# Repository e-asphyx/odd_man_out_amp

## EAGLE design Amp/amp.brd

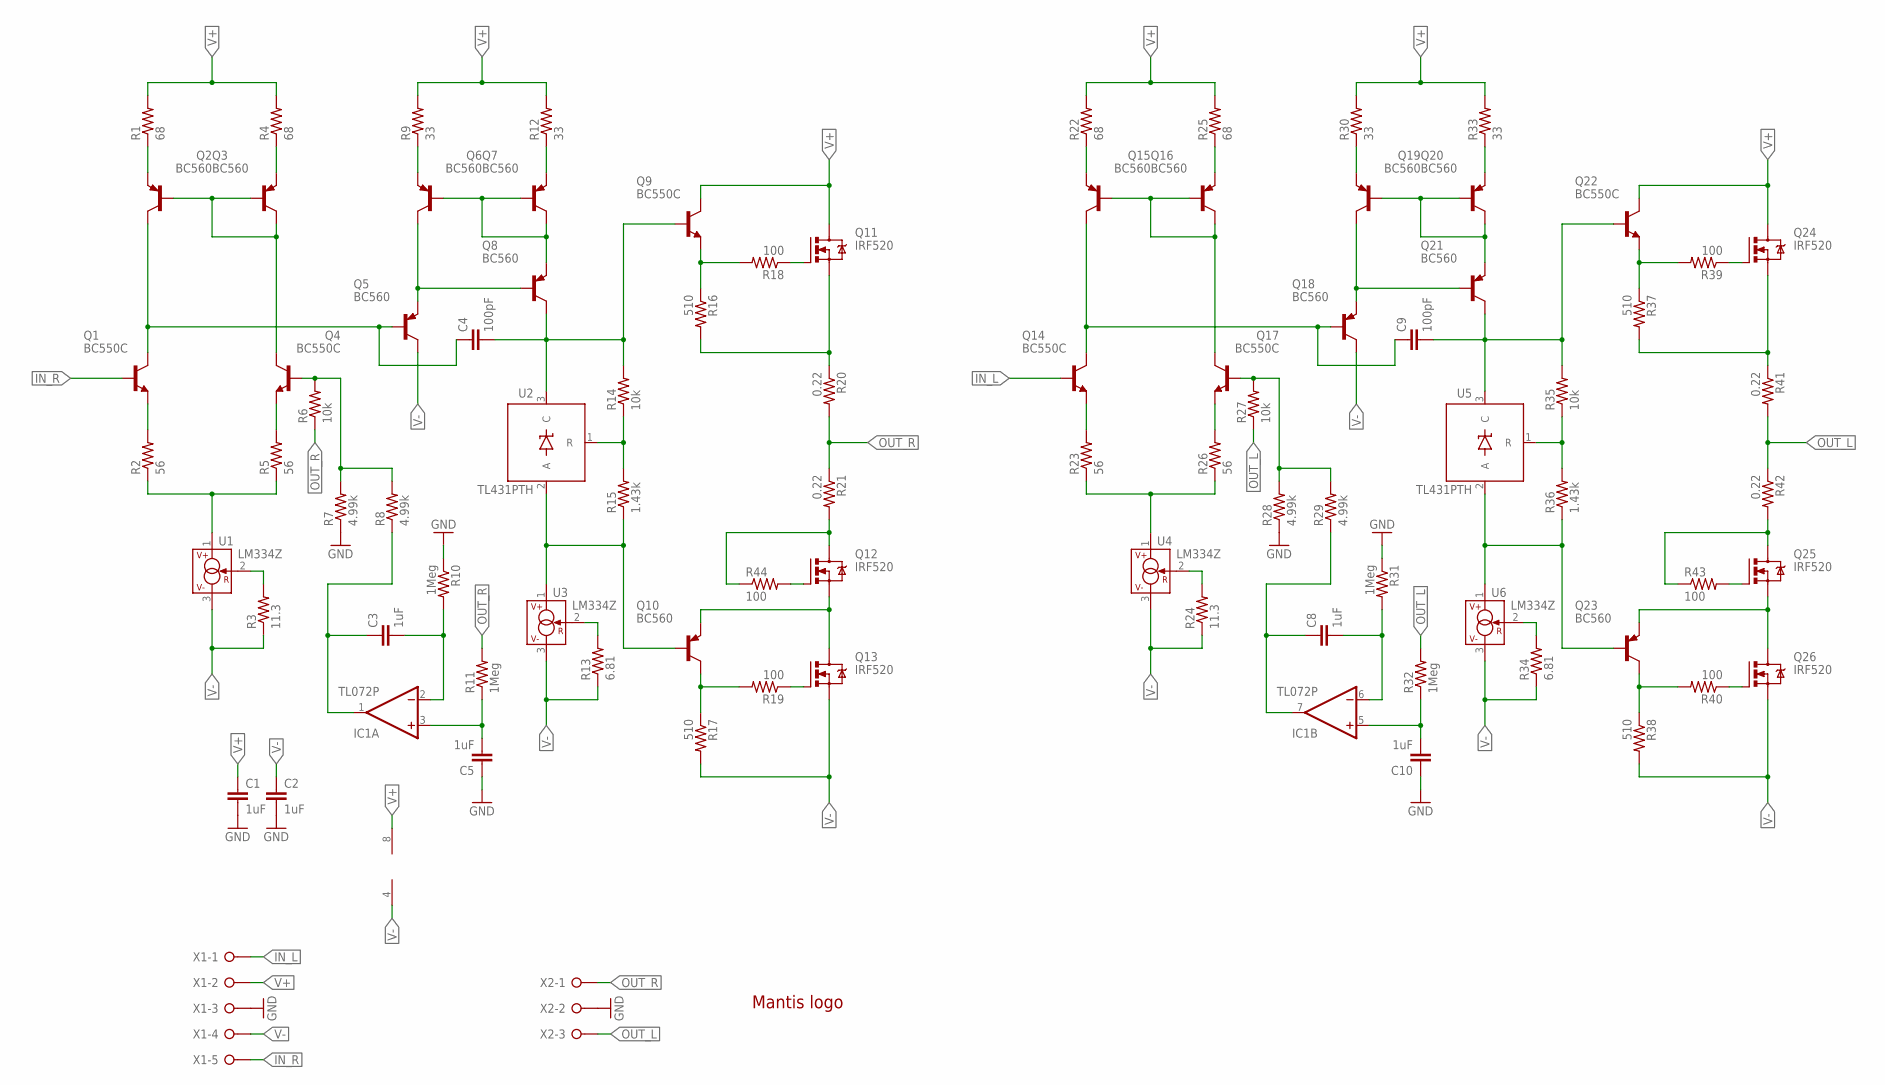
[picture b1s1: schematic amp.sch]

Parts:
C1, C2: 1uF; CAP-PTH-SMALL
C3, C5, C8, C10: 1uF; C5B5.5
C4, C9: 100pF; C5B4.5
IC1: TL072P; DIL08
LOGO1: LOGO-MANTIS
Q1, Q4, Q9, Q14, Q17, Q22: BC550C; TO92-EBC
Q2, Q3, Q5, Q6, Q7, Q8, Q10, Q15, Q16, Q18, Q19, Q20, Q21, Q23: BC560; TO92-EBC
Q11, Q12, Q13, Q24, Q25, Q26: IRF520; TO220BV
R1, R4, R22, R25: 68; AXIAL-0.4
R2, R5, R23, R26: 56; AXIAL-0.4
R3, R24: 11.3; AXIAL-0.4
R6, R14, R27, R35: 10k; AXIAL-0.4
R7, R8, R28, R29: 4.99k; AXIAL-0.4
R9, R12, R30, R33: 33; AXIAL-0.4
R10, R11, R31, R32: 1Meg; AXIAL-0.4
R13, R34: 6.81; AXIAL-0.4
R15, R36: 1.43k; AXIAL-0.4
R16, R17, R37, R38: 510; AXIAL-0.4
R18, R19, R39, R40, R43, R44: 100; AXIAL-0.4
R20, R21, R41, R42: 0.22; AXIAL-0.4
U1, U3, U4, U6: LM334Z; TO-92
U2, U5: TL431PTH; TO-92
X1: W237-05P; W237-5P
X2: W237-3E

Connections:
GND: C1.2, C2.2, C5.1, C10.1, R7.P$1 (1), R10.P$1 (1), R28.P$1 (1), R31.P$1 (1), X1.3, X2.2
IN_L: Q14.B, X1.1
IN_R: Q1.B, X1.5
unnamed: Q2.B, Q3.B, Q3.C, Q4.C
unnamed: C4.1, Q1.C, Q2.C, Q5.B
unnamed: Q2.E, R1.P$1 (1)
unnamed: Q3.E, R4.P$1 (1)
unnamed: Q1.E, R2.P$2 (2)
unnamed: Q4.E, R5.P$2 (2)
unnamed: R2.P$1 (1), R5.P$1 (1), U1.1 (V+)
unnamed: R3.P$2 (2), U1.2 (R)
unnamed: Q6.B, Q7.B, Q7.C, Q8.E
unnamed: Q6.E, R9.P$1 (1)
unnamed: Q7.E, R12.P$1 (1)
unnamed: Q5.E, Q6.C, Q8.B
unnamed: C4.2, Q8.C, Q9.B, R14.P$2 (2), U2.3 (C)
unnamed: R14.P$1 (1), R15.P$2 (2), U2.1 (R)
unnamed: Q10.B, R15.P$1 (1), U2.2 (A), U3.1 (V+)
unnamed: Q13.G, R19.P$1 (1)
unnamed: R13.P$2 (2), U3.2 (R)
unnamed: Q10.C, R17.P$1 (1), R19.P$2 (2)
unnamed: Q9.E, R16.P$1 (1), R18.P$2 (2)
unnamed: Q11.G, R18.P$1 (1)
unnamed: Q10.E, Q12.S, Q13.D
unnamed: C3.1, IC1.1 (OUT), R8.P$1 (1)
unnamed: Q11.S, R16.P$2 (2), R20.P$1 (1)
unnamed: C3.2, IC1.2 (-IN), R10.P$2 (2)
unnamed: Q12.D, R21.P$2 (2), R44.P$1 (1)
unnamed: C5.2, IC1.3 (+IN), R11.P$1 (1)
unnamed: Q15.B, Q16.B, Q16.C, Q17.C
unnamed: Q4.B, R6.P$2 (2), R7.P$2 (2), R8.P$2 (2)
unnamed: Q15.E, R22.P$1 (1)
unnamed: Q16.E, R25.P$1 (1)
unnamed: C9.1, Q14.C, Q15.C, Q18.B
unnamed: Q14.E, R23.P$2 (2)
unnamed: Q17.E, R26.P$2 (2)
unnamed: R23.P$1 (1), R26.P$1 (1), U4.1 (V+)
unnamed: R24.P$2 (2), U4.2 (R)
unnamed: Q19.B, Q20.B, Q20.C, Q21.E
unnamed: Q19.E, R30.P$1 (1)
unnamed: Q20.E, R33.P$1 (1)
unnamed: Q18.E, Q19.C, Q21.B
unnamed: C9.2, Q21.C, Q22.B, R35.P$2 (2), U5.3 (C)
unnamed: R35.P$1 (1), R36.P$2 (2), U5.1 (R)
unnamed: Q23.B, R36.P$1 (1), U5.2 (A), U6.1 (V+)
unnamed: R34.P$2 (2), U6.2 (R)
unnamed: Q25.G, R43.P$2 (2)
unnamed: Q12.G, R44.P$2 (2)
unnamed: Q23.E, Q25.S, Q26.D
unnamed: Q24.S, R37.P$2 (2), R41.P$1 (1)
unnamed: Q25.D, R42.P$2 (2), R43.P$1 (1)
unnamed: C8.1, IC1.7 (OUT), R29.P$1 (1)
unnamed: C8.2, IC1.6 (-IN), R31.P$2 (2)
unnamed: C10.2, IC1.5 (+IN), R32.P$1 (1)
unnamed: Q17.B, R27.P$2 (2), R28.P$2 (2), R29.P$2 (2)
unnamed: Q26.G, R40.P$1 (1)
unnamed: Q23.C, R38.P$1 (1), R40.P$2 (2)
unnamed: Q22.E, R37.P$1 (1), R39.P$2 (2)
unnamed: Q24.G, R39.P$1 (1)
OUT_L: R27.P$1 (1), R32.P$2 (2), R41.P$2 (2), R42.P$1 (1), X2.3
OUT_R: R6.P$1 (1), R11.P$2 (2), R20.P$2 (2), R21.P$1 (1), X2.1
V+: C1.1, IC1.8 (V+), Q9.C, Q11.D, Q22.C, Q24.D, R1.P$2 (2), R4.P$2 (2), R9.P$2 (2), R12.P$2 (2), R22.P$2 (2), R25.P$2 (2), R30.P$2 (2), R33.P$2 (2), X1.2
V-: C2.1, IC1.4 (V-), Q5.C, Q13.S, Q18.C, Q26.S, R3.P$1 (1), R13.P$1 (1), R17.P$2 (2), R24.P$1 (1), R34.P$1 (1), R38.P$2 (2), U1.3 (V-), U3.3 (V-), U4.3 (V-), U6.3 (V-), X1.4

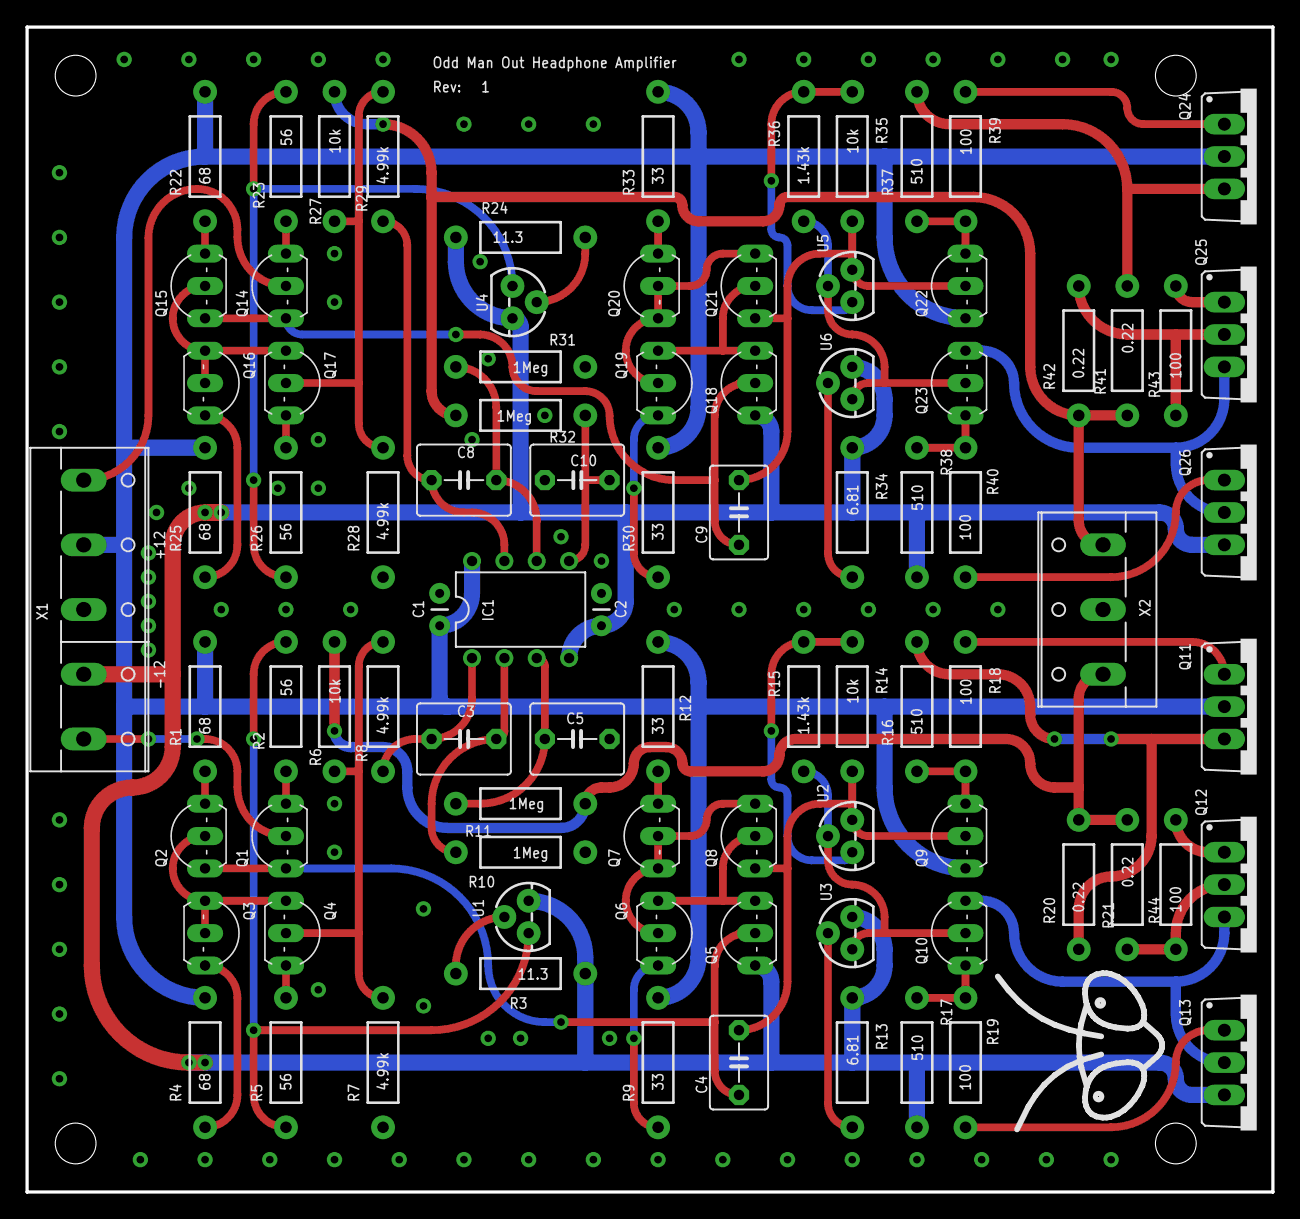
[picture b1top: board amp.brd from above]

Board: 2 copper layers, 97.8 x 91.4 mm, 88 parts (0 on the bottom side), 63 nets.

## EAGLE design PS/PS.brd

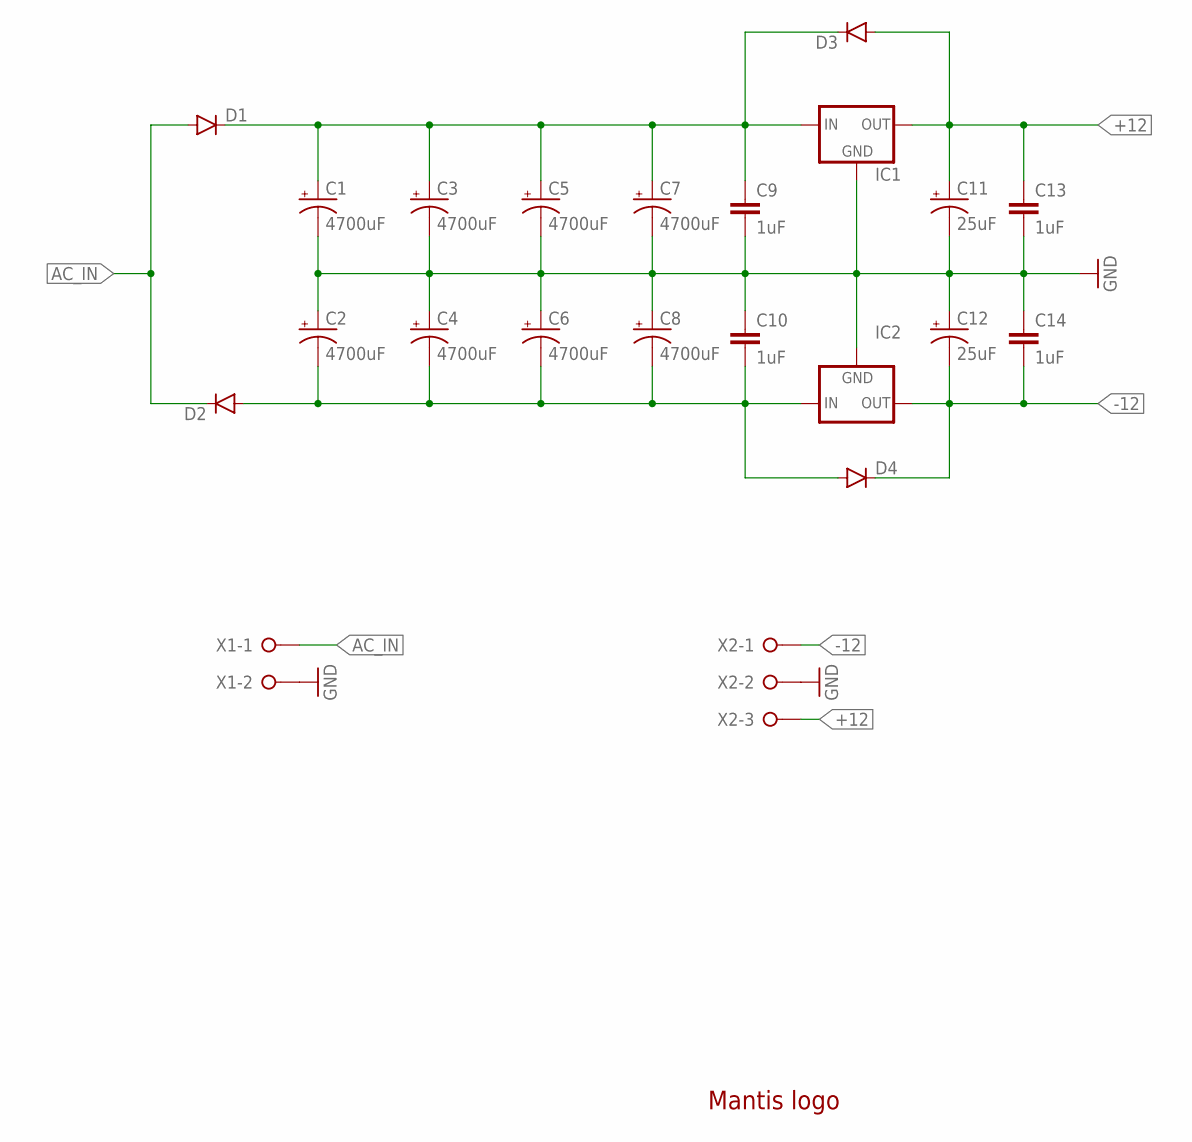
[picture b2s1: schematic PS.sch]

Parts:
C1, C2, C3, C4, C5, C6, C7, C8: 4700uF; CPOL-RADIAL-1000UF-63V
C9, C10, C13, C14: 1uF; CAP-PTH-SMALL
C11, C12: 25uF; CPOL-RADIAL-10UF-25V
D1, D2, D3, D4: DIODEPTH; DIODE-1N4001
IC1: 78XXL
IC2: 79XXL
LOGO1: LOGO-MANTIS
X1: W237-02P; W237-132
X2: W237-3E

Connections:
+12: C11.1 (+), C13.1, D3.A, IC1.OUT, X2.3
-12: C12.2 (-), C14.2, D4.C, IC2.OUT, X2.1
AC_IN: D1.A, D2.C, X1.1
GND: C1.2 (-), C2.1 (+), C3.2 (-), C4.1 (+), C5.2 (-), C6.1 (+), C7.2 (-), C8.1 (+), C9.2, C10.1, C11.2 (-), C12.1 (+), C13.2, C14.1, IC1.GND, IC2.GND, X1.2, X2.2
R+: C1.1 (+), C3.1 (+), C5.1 (+), C7.1 (+), C9.1, D1.C, D3.C, IC1.IN
R-: C2.2 (-), C4.2 (-), C6.2 (-), C8.2 (-), C10.2, D2.A, D4.A, IC2.IN

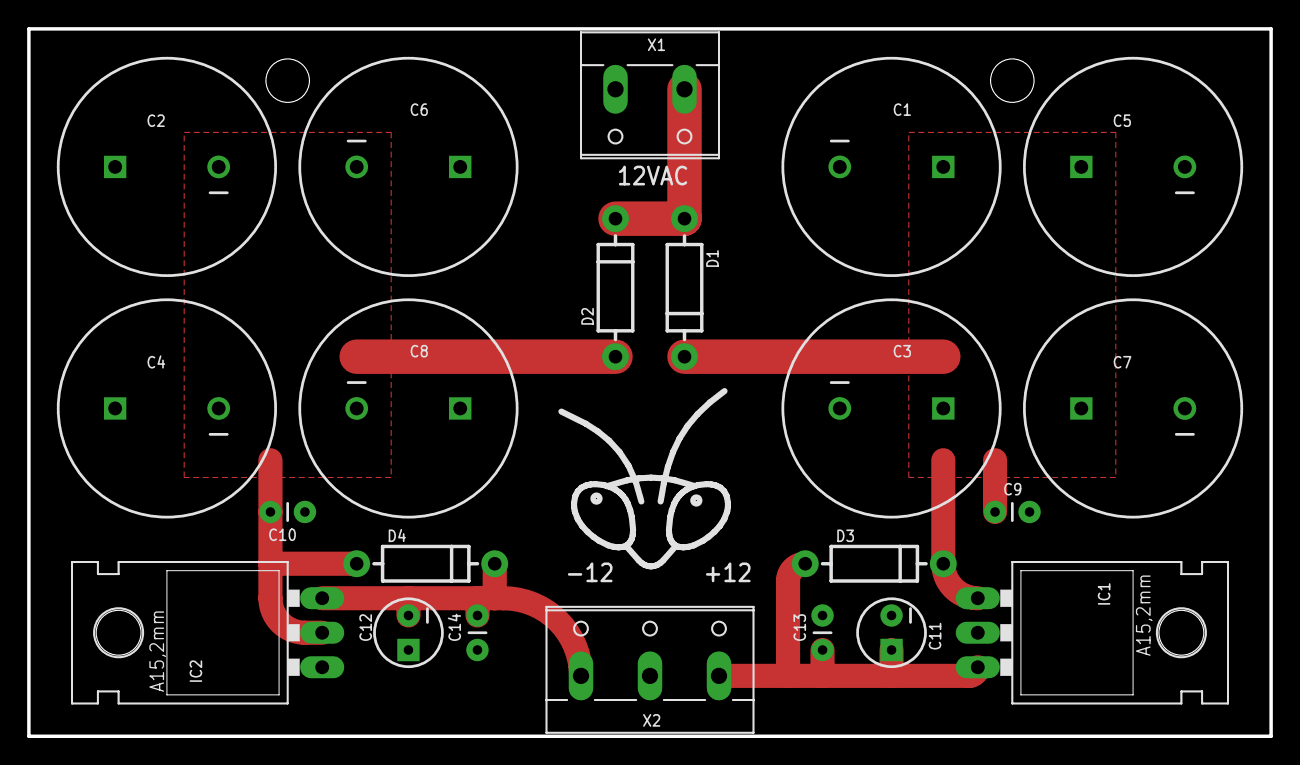
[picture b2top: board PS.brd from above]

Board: 2 copper layers, 91.4 x 52.1 mm, 23 parts (0 on the bottom side), 6 nets.

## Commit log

2016-10-09 Initial
2016-10-09 Oops
2016-10-09 Need to sleep more
2016-10-09 Small fix
2016-10-09 Second channel
2016-10-10 Power supply
2016-10-12 More gate stoppers

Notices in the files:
parts and their libraries:
SparkFun-Resistors: Licensing: Creative Commons ShareAlike 4.0 International - https://creativecommons.org/licenses/by-sa/4.0
